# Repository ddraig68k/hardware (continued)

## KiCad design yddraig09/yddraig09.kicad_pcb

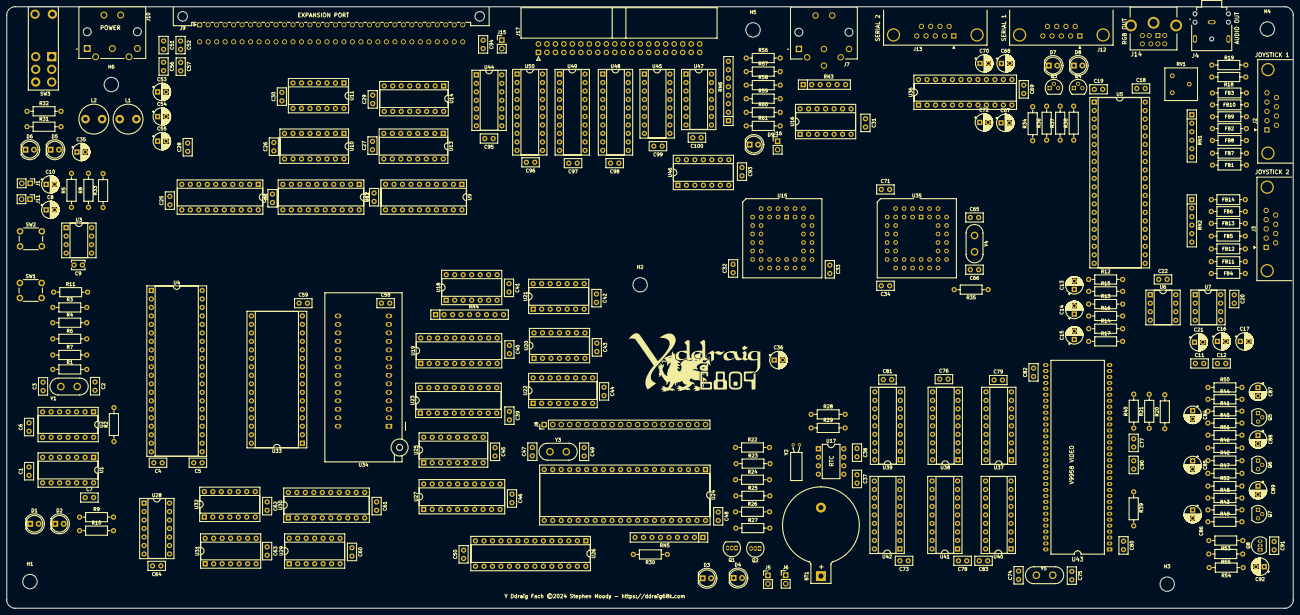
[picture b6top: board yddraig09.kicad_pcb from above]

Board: 4 copper layers, 385.0 x 180.0 mm, 283 parts (0 on the bottom side), 366 nets, no tracks yet.

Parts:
BT1: CR2032; BatteryHolder_Keystone_103_1x20mm
C1, C4, C5, C6, C18, C19, C20, C22, C23, C24, C25, C26, C27, C28, C29, C30, C31, C32, C33, C34, C37, C38, C39, C40, C41, C42, C43, C44, C45, C46, C48, C50, C51, C52, C56, C57, C58, C59, C60, C61, C62, C63, C64, C69, C71, C73, C76, C77, C78, C79, C80, C81, C82, C83, C90, C91, C93, C94, C95, C96, C97, C98, C99, C100: 100nF; C_Disc_D5.0mm_W2.5mm_P2.50mm
C2, C3, C47, C49, C65, C66, C74, C75: 22pF; C_Disc_D5.0mm_W2.5mm_P2.50mm
C7: 5pF; C_Disc_D5.0mm_W2.5mm_P2.50mm
C8, C10, C13, C14, C15, C16, C84, C85, C86: 10uF; CP_Radial_D5.0mm_P2.50mm
C9: 10nF; C_Disc_D3.8mm_W2.6mm_P2.50mm
C11, C12: 100nf; C_Disc_D5.0mm_W2.5mm_P2.50mm
C17: 1uF; CP_Radial_D5.0mm_P2.50mm
C21, C87, C88, C89, C92: 220uF; CP_Radial_D5.0mm_P2.50mm
C35, C36, C53, C54, C55: 47uF; CP_Radial_D5.0mm_P2.50mm
C67, C68, C70, C72: 0.1uF; CP_Radial_D5.0mm_P2.50mm
D1, D2, D3, D4, D5, D6, D7, D8: GREEN; LED_D5.0mm
D9: BLUE; LED_D5.0mm
FB1, FB2, FB3, FB4, FB5, FB6, FB7, FB8, FB9, FB10, FB11, FB12, FB13, FB14: 1mH; L_Axial_L6.6mm_D2.7mm_P10.16mm_Horizontal_Vishay_IM-2
H1, H2, H3, H4, H5, H6: MountingHole; MountingHole_4.3mm_M4
J1: ExtReset; PinHeader_1x02_P2.54mm_Vertical
J2: Joystick 2; DSUB-9_Male_Horizontal_P2.77x2.84mm_EdgePinOffset4.94mm_Hou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
J3: Joystick 1; DSUB-9_Male_Horizontal_P2.77x2.84mm_EdgePinOffset4.94mm_Hou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
J4: Audio Out; SWITCHCRAFT_35RAPC2BHN2
J5: ExtUSR1; PinHeader_1x02_P2.54mm_Vertical
J6: ExtUSR2; PinHeader_1x02_P2.54mm_Vertical
J7: IEC PORT; CUI_SDS-60J
J8: Keyboard; PinHeader_1x20_P2.54mm_Vertical
J9: Expansion; DIN41612_C_2x32_Male_Horizontal_THT
J10: 57PC5F; SWITCHCRAFT_57PC5F
J11: PwrLED; PinHeader_1x02_P2.54mm_Vertical
J12: Serial 1; DSUB-9_Male_Horizontal_P2.77x2.84mm_EdgePinOffset4.94mm_Hou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
J13: Serial 2; DSUB-9_Male_Horizontal_P2.77x2.84mm_EdgePinOffset4.94mm_Hou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
J14: RGB Video; MINI-DIN-8-TE_57492681
J15: IDE 5V; PinHeader_1x02_P2.54mm_Vertical
J16: IDE LED; PinHeader_1x02_P2.54mm_Vertical
J17: IDE_Interface; IDC-Header_2x20_P2.54mm_Horizontal
L1, L2: 22uH; L_Radial_D8.7mm_P5.00mm_Fastron_07HCP
Q1, Q2: BC549; TO-92_Inline
Q3, Q4, Q5, Q6, Q7: 2N4403; TO-92
Q8: 2N3904; TO-92_Inline
R1: 4M7; R_Axial_DIN0207_L6.3mm_D2.5mm_P10.16mm_Horizontal
R2: 2K2; R_Axial_DIN0207_L6.3mm_D2.5mm_P10.16mm_Horizontal
R3, R4, R6, R7: 4k7; R_Axial_DIN0207_L6.3mm_D2.5mm_P10.16mm_Horizontal
R5, R30, R35, R56, R57, R58, R59: 10K; R_Axial_DIN0207_L6.3mm_D2.5mm_P10.16mm_Horizontal
R8: 38K; R_Axial_DIN0207_L6.3mm_D2.5mm_P10.16mm_Horizontal
R9, R10, R12, R13, R14, R20, R21, R22, R25, R41, R42, R43, R53: 1K; R_Axial_DIN0207_L6.3mm_D2.5mm_P10.16mm_Horizontal
R11, R15, R16, R17, R28, R29, R39, R40: 4K7; R_Axial_DIN0207_L6.3mm_D2.5mm_P10.16mm_Horizontal
R18, R19, R50, R51, R52, R54: 100R; R_Axial_DIN0207_L6.3mm_D2.5mm_P10.16mm_Horizontal
R23, R24, R26, R27, R60, R61: 330R; R_Axial_DIN0207_L6.3mm_D2.5mm_P10.16mm_Horizontal
R31: 270R; R_Axial_DIN0207_L6.3mm_D2.5mm_P10.16mm_Horizontal
R32: 750R; R_Axial_DIN0207_L6.3mm_D2.5mm_P10.16mm_Horizontal
R33, R34, R36, R37, R38: 150R; R_Axial_DIN0207_L6.3mm_D2.5mm_P10.16mm_Horizontal
R44, R46, R48: 27K; R_Axial_DIN0207_L6.3mm_D2.5mm_P10.16mm_Horizontal
R45, R47, R49: 12K; R_Axial_DIN0207_L6.3mm_D2.5mm_P10.16mm_Horizontal
R55: 220R; R_Axial_DIN0207_L6.3mm_D2.5mm_P10.16mm_Horizontal
RN1, RN2: 4K7; R_Array_SIP6
RN3: 10K; R_Array_SIP6
RN4: 4K7; R_Array_SIP9
RN5: 10K; R_Array_SIP9
RN6: 22R; R_Array_SIP8
RV1: 10K; Potentiometer_Bourns_3386F_Vertical
SW1: NMI; SW_PUSH_6mm_H4.3mm
SW2: Reset; SW_PUSH_6mm_H4.3mm
SW3: PowerSwitch; M2022_Rocker_Switch
U1: 74LS73; DIP-14_W7.62mm_Socket
U2: 74HCT04; DIP-14_W7.62mm_Socket
U3: NE555P; DIP-8_W7.62mm_Socket
U4: MC68B09E; DIP-40_W15.24mm_Socket
U5: YM2203; DIP-40_W15.24mm_Socket
U6: YM3014B; DIP-8_W7.62mm_Socket
U7: NE5532; DIP-8_W7.62mm_Socket
U8, U9, U12, U50: 74LS245; DIP-20_W7.62mm_Socket
U10, U13, U25: 74LS138; DIP-16_W7.62mm_Socket
U11: 74LS21; DIP-14_W7.62mm_Socket
U14, U45: 74LS139; DIP-16_W7.62mm_Socket
U15: W65C22S; PLCC-44_THT-Socket
U16: 74LS06; DIP-14_W7.62mm_Socket
U17: DS1307+; DIP-8_W7.62mm
U18, U20, U28, U46: 74LS32; DIP-14_W7.62mm_Socket
U19, U48, U49: 74LS574; DIP-20_W7.62mm_Socket
U21: 74LS11; DIP-14_W7.62mm_Socket
U22: 74LS147; DIP-16_W7.62mm_Socket
U23: 74LS540; DIP-20_W7.62mm_Socket
U24: AT89C51-24PI; DIP-40_W15.24mm_Socket
U26: IDT7201; DIP-28_W7.62mm_Socket
U27: 74HCT541; DIP-20_W7.62mm_Socket
U29: 74LS27; DIP-14_W7.62mm_Socket
U30: 74HCT273; DIP-20_W7.62mm_Socket
U31, U32, U44: 74LS08; DIP-14_W7.62mm_Socket
U33: AS6C4008-55PCN; DIP-32_W15.24mm_Socket
U34: AT28C256B; DIP_Socket-28_W11.9_W12.7_W15.24_W17.78_W18.5_3M_228-1277-0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
U35: SC26C92C1A; PLCC-44_THT-Socket
U36: MAX208; DIP-24_W7.62mm_Socket
U37, U38, U39, U40, U41, U42: 41464; DIP-18_W7.62mm_Socket
U43: V9958; DIP-64-V9958
U47: 74LS74; DIP-14_W7.62mm_Socket
Y1: 8Mhz; Crystal_HC50_Vertical
Y2: Crystal; Crystal_C38-LF_D3.0mm_L8.0mm_Horizontal
Y3: 12Mhz; Crystal_HC50_Vertical
Y4: 3.6864Mhz; Crystal_HC50_Vertical
Y5: 21.443Mhz; Crystal_HC50_Vertical

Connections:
+5V: C1.1, C4.1, C5.1, C6.1, C18.1, C19.1, C20.1, C21.1, C22.1, C23.1, C24.1, C25.1, C26.1, C27.1, C28.1, C29.1, C30.1, C31.1, C32.1, C33.1, C34.1, C35.1, C36.1, C37.1, C38.1, C39.1, C40.1, C41.1, C42.1, C43.1, C44.1, C45.1, C46.1, C48.1, C50.1, C54.1, C55.1, C56.1, C57.1, C58.1, C59.1, C60.1, C61.1, C62.1, C63.1, C64.1, C69.1, C71.1, C72.2, C73.1, C76.1, C77.1, C78.1, C79.1, C80.1, C81.1, C83.1, C90.1, C91.1, C93.1, C94.1, C95.1, C96.1, C97.1, C98.1, C99.1, C100.1, D5.2 (A), D9.2 (A), FB2.1, FB5.1, J9.A1, J9.C1, J11.1, J14.5, J15.2, J16.2, L2.2, Q3.1 (E), Q4.1 (E), Q8.3 (C), R3.1, R4.1, R5.1, R6.1, R7.1, R8.1, R20.1, R21.1, R23.1, R24.1, R26.1, R27.1, R28.1, R29.1, R30.1, R35.1, R39.2, R40.2, R44.1, R46.1, R48.1, R50.1, R51.1, R52.1, R56.2, R58.2, R59.2, RN1.1 (common), RN2.1 (common), RN3.1 (common), RN4.1 (common), RN5.1 (common), U1.2 (~R), U1.4 (VCC), U1.6 (~R), U2.14 (VCC), U3.4 (R), U3.8 (VCC), U4.7 (VCC), U5.21 (VDD), U6.1 (VDD), U7.8 (V+), U8.20 (VCC), U9.20 (VCC), U10.6 (E3), U10.16 (VCC), U11.9, U11.10, U11.14 (VCC), U12.20 (VCC), U13.6 (E3), U13.16 (VCC), U14.16 (VCC), U15.21 (VDD), U15.26 (CS1), U16.14 (VCC), U17.8 (VCC), U18.14 (VCC), U19.20 (VCC), U20.14 (VCC), U21.14 (VCC), U22.5 (E8), U22.10 (E9), U22.16 (VCC), U23.6 (A4), U23.7 (A5), U23.8 (A6), U23.9 (A7), U23.20 (VCC), U24.40 (VCC), U25.6 (E3), U25.16 (VCC), U26.23 (FL), U26.28 (VCC), U27.20 (VCC), U28.14 (VCC), U29.14 (VCC), U30.20 (VCC), U31.14 (VCC), U32.14 (VCC), U33.32 (VCC), U34.28 (VCC), U35.44 (VCC), U36.9 (VCC), U37.9 (VCC), U38.9 (VCC), U39.9 (VCC), U40.9 (VCC), U41.9 (VCC), U42.9 (VCC), U43.21 (VDD/DAC), U43.58 (VDD), U44.14 (VCC), U45.16 (VCC), U46.14 (VCC), U47.14 (VCC), U48.20 (VCC), U49.20 (VCC), U50.20 (VCC)
+12V: C51.1, C52.1, C53.1, D6.2 (A), J9.A2, J9.C2, L1.2
/6809 CPU/CLK_8MHZ: C7.1, R2.1, U1.1 (C), U1.5 (C)
/6809 CPU/CLOCK_E: J9.C8, U1.10 (K), U1.12 (Q), U4.34 (E), U5.38 (CLK-M), U14.3 (A1), U15.27 (PHI2), U47.3 (C), U47.11 (C)
/6809 CPU/CLOCK_Q: J9.C7, U1.9 (Q), U1.14 (J), U4.35 (Q)
/6809 CPU/CPU_A0: U4.8 (A0), U9.18 (B0), U33.12 (A0), U34.10 (A0)
/6809 CPU/CPU_A1: U4.9 (A1), U9.17 (B1), U33.11 (A1), U34.9 (A1)
/6809 CPU/CPU_A2: U4.10 (A2), U9.16 (B2), U33.10 (A2), U34.8 (A2)
/6809 CPU/CPU_A3: U4.11 (A3), U9.15 (B3), U33.9 (A3), U34.7 (A3)
/6809 CPU/CPU_A4: U4.12 (A4), U9.14 (B4), U33.8 (A4), U34.6 (A4)
/6809 CPU/CPU_A5: U4.13 (A5), U9.13 (B5), U13.1 (A0), U33.7 (A5), U34.5 (A5)
/6809 CPU/CPU_A6: U4.14 (A6), U9.12 (B6), U13.2 (A1), U33.6 (A6), U34.4 (A6)
/6809 CPU/CPU_A7: U4.15 (A7), U9.11 (B7), U13.3 (A2), U33.5 (A7), U34.3 (A7)
/6809 CPU/CPU_A8: U4.16 (A8), U12.18 (B0), U33.27 (A8), U34.25 (A8)
/6809 CPU/CPU_A9: U4.17 (A9), U12.17 (B1), U33.26 (A9), U34.24 (A9)
/6809 CPU/CPU_A10: U4.18 (A10), U12.16 (B2), U33.23 (A10), U34.21 (A10)
/6809 CPU/CPU_A11: U4.19 (A11), U12.15 (B3), U33.25 (A11), U34.23 (A11)
/6809 CPU/CPU_A12: U4.20 (A12), U12.14 (B4), U33.4 (A12), U34.2 (A12)
/6809 CPU/CPU_A13: U4.21 (A13), U10.1 (A0), U12.13 (B5), U33.28 (A13), U34.26 (A13)
/6809 CPU/CPU_A14: U4.22 (A14), U10.2 (A1), U12.12 (B6)
/6809 CPU/CPU_A15: U4.23 (A15), U10.3 (A2), U12.11 (B7)
/6809 CPU/RD~WR: U4.32 (R/~W), U8.1 (A->B), U14.2 (A0)
/6809 CPU/RESET: J9.C6, U2.13, U3.3 (Q), U24.9 (RESET), U35.38 (RESET)
/6809 CPU/~FIRQ: J9.C4, R4.2, U4.4 (~FIRQ)
/6809 CPU/~HALT: J9.A4, R3.2, U4.40 (~HALT)
/6809 CPU/~IRQ: R6.2, U4.3 (~IRQ), U21.12
/6809 CPU/~NMI: J9.C3, R7.2, SW1.2 (B), U4.2 (~NMI)
/6809 CPU/~RESET: J9.C5, J17.1 (~RESET), U2.12, U4.37 (~RESET), U5.24 (~RESET), U15.37 (~RESET), U16.9, U30.1 (~Mr), U43.9 (~RESET)
/Audio/A0: J9.C30, RN6.1 (R1.1), U5.37 (A0), U9.2 (A0), U15.42 (RS0), U25.1 (A0), U35.2 (A0), U43.29 (MODE0)
/Audio/A1: J9.C29, RN6.3 (R2.1), U9.3 (A1), U15.41 (RS1), U35.4 (A1), U43.28 (MODE1)
/Audio/A2: J9.C28, RN6.5 (R3.1), U9.4 (A2), U15.40 (RS2), U35.6 (A2)
/Audio/A3: J9.C27, RN6.7 (R4.1), U9.5 (A3), U15.39 (RS3), U35.7 (A3)
/Audio/A4: J9.C26, U9.6 (A4)
/Audio/A5: J9.C25, U9.7 (A5)
/Audio/A6: J9.C24, U9.8 (A6)
/Audio/A7: J9.C23, U9.9 (A7)
/Audio/A8: J9.C22, U12.2 (A0)
/Audio/A9: J9.C21, U12.3 (A1)
/Audio/A10: J9.C20, U12.4 (A2)
/Audio/A11: J9.C19, U12.5 (A3)
/Audio/A12: J9.C18, U12.6 (A4)
/Audio/A13: J9.C17, U12.7 (A5)
/Audio/A14: J9.C16, U12.8 (A6)
/Audio/A15: J9.C15, U12.9 (A7)
/Audio/AUDIO_L: J4.1, J14.1, R18.2
/Audio/AUDIO_OUT: C17.2, R15.1, R16.1, R17.1, RV1.1
/Audio/AUDIO_R: J4.3, J14.2, R19.2
/Audio/D0: J9.A12, U5.40 (D0), U8.2 (A0), U15.36 (D0), U19.2 (D0), U23.18 (Y0), U26.9 (Q0), U27.18 (Y0), U35.28 (D0), U43.40 (D0), U50.2 (A0)
/Audio/D1: J9.A11, U5.2 (D1), U8.3 (A1), U15.35 (D1), U19.3 (D1), U23.17 (Y1), U26.10 (Q1), U27.17 (Y1), U35.18 (D1), U43.39 (D1), U50.3 (A1)
/Audio/D2: J9.A10, U5.3 (D2), U8.4 (A2), U15.34 (D2), U19.4 (D2), U23.16 (Y2), U26.11 (Q2), U27.16 (Y2), U35.27 (D2), U43.38 (D2), U50.4 (A2)
/Audio/D3: J9.A9, U5.4 (D3), U8.5 (A3), U15.32 (D3), U19.5 (D3), U23.15 (Y3), U26.12 (Q3), U27.15 (Y3), U35.19 (D3), U43.37 (D3), U50.5 (A3)
/Audio/D4: J9.A8, U5.5 (D4), U8.6 (A4), U15.31 (D4), U19.6 (D4), U23.14 (Y4), U26.16 (Q4), U27.14 (Y4), U35.26 (D4), U43.36 (D4), U50.6 (A4)
/Audio/D5: J9.A7, U5.6 (D5), U8.7 (A5), U15.30 (D5), U19.7 (D5), U23.13 (Y5), U26.17 (Q5), U27.13 (Y5), U35.20 (D5), U43.35 (D5), U50.7 (A5)
/Audio/D6: J9.A6, U5.7 (D6), U8.8 (A6), U15.29 (D6), U19.8 (D6), U23.12 (Y6), U26.18 (Q6), U27.12 (Y6), U35.25 (D6), U43.34 (D6), U50.8 (A6)
/Audio/D7: J9.A5, U5.8 (D7), U8.9 (A7), U15.28 (D7), U19.9 (D7), U23.11 (Y7), U26.19 (Q7), U27.11 (Y7), U35.21 (D7), U43.32 (D7), U50.9 (A7)
/Audio/~CS_SND: U5.34 (~CS), U13.10 (O5)
/Audio/~IRQ_SND: RN4.6 (R5), U5.25 (~IRQ), U20.1
/Decode Logic/~BANKSEL: U13.15 (O0), U30.11 (Cp)
/Decode Logic/~CS_EXP: J9.A15, U10.11 (O4)
/Decode Logic/~CS_IDE: U13.14 (O1), U44.5, U46.2, U46.5
/Decode Logic/~CS_IRQEN: U13.7 (O7), U18.12, U23.19 (G2)
/Decode Logic/~CS_KBD: U13.12 (O3), U25.4 (E1)
/Decode Logic/~CS_RAM: U11.6, U33.22 (CE#)
/Decode Logic/~CS_ROM: U11.8, U34.20 (~CE)
/Decode Logic/~CS_UART: U13.13 (O2), U35.39 (~CE)
/Decode Logic/~CS_VDP: U13.11 (O4), U14.15 (E)
/Decode Logic/~CS_VIA: U13.9 (O6), U15.25 (~CS2)
/Decode Logic/~IOSEL: U10.10 (O5), U13.5 (E2)
/Decode Logic/~MEM0: U10.15 (O0), U11.1
/Decode Logic/~MEM2: U10.14 (O1), U11.2
/Decode Logic/~MEM4: U10.13 (O2), U11.4
/Decode Logic/~MEM6: U10.12 (O3), U11.5
/Decode Logic/~MEMC: U10.9 (O6), U11.12
/Decode Logic/~MEME: U10.7 (O7), U11.13
/Decode Logic/~VDP_RD: R20.2, U14.11 (O1), U43.31 (~CSR)
/Decode Logic/~VDP_WR: R21.2, U14.10 (O2), U43.30 (~CSW)
/IDE Interface/IDE_A0: J17.35 (A0), RN6.2 (R1.2)
/IDE Interface/IDE_A1: J17.33 (A1), RN6.4 (R2.2)
/IDE Interface/IDE_A2: J17.36 (A2), RN6.6 (R3.2)
/IDE Interface/IDE_A3: RN6.8 (R4.2), U45.2 (A0), U45.14 (A0), U46.9
/IDE Interface/IDE_ACTIVE: J17.39 (~ACTIVE), R60.2, R61.2
/IDE Interface/IDE_D0: J17.17 (D0), U48.19 (Q0), U49.2 (D0), U50.18 (B0)
/IDE Interface/IDE_D1: J17.15 (D1), U48.18 (Q1), U49.3 (D1), U50.17 (B1)
/IDE Interface/IDE_D2: J17.13 (D2), U48.17 (Q2), U49.4 (D2), U50.16 (B2)
/IDE Interface/IDE_D3: J17.11 (D3), U48.16 (Q3), U49.5 (D3), U50.15 (B3)
/IDE Interface/IDE_D4: J17.9 (D4), U48.15 (Q4), U49.6 (D4), U50.14 (B4)
/IDE Interface/IDE_D5: J17.7 (D5), U48.14 (Q5), U49.7 (D5), U50.13 (B5)
/IDE Interface/IDE_D6: J17.5 (D6), U48.13 (Q6), U49.8 (D6), U50.12 (B6)
/IDE Interface/IDE_D7: J17.3 (D7), U48.12 (Q7), U49.9 (D7), U50.11 (B7)
/IDE Interface/IDE_D8: J17.4 (D8), U48.2 (D0), U49.19 (Q0)
/IDE Interface/IDE_D9: J17.6 (D9), U48.3 (D1), U49.18 (Q1)
/IDE Interface/IDE_D10: J17.8 (D10), U48.4 (D2), U49.17 (Q2)
/IDE Interface/IDE_D11: J17.10 (D11), U48.5 (D3), U49.16 (Q3)
/IDE Interface/IDE_D12: J17.12 (D12), U48.6 (D4), U49.15 (Q4)
/IDE Interface/IDE_D13: J17.14 (D13), U48.7 (D5), U49.14 (Q5)
/IDE Interface/IDE_D14: J17.16 (D14), U48.8 (D6), U49.13 (Q6)
/IDE Interface/IDE_D15: J17.18 (D15), U48.9 (D7), U49.12 (Q7)
/IO/ATN_OUT: U15.4 (PA2), U16.1
/IO/CLK_IN: J7.4, RN3.4 (R3), U15.6 (PA4), U16.6
/IO/CLK_OUT: U15.3 (PA1), U16.5
/IO/DATA_IN: J7.5, RN3.6 (R5), U15.5 (PA3), U16.4
/IO/DATA_OUT: U15.2 (PA0), U16.3
/IO/EXPIO_C1: J9.A19, U15.19 (CB1)
/IO/EXPIO_C2: J9.A20, U15.20 (CB2)
/IO/EXPIO_P0: J9.A23, U15.10 (PB0)
/IO/EXPIO_P1: J9.A24, U15.12 (PB1)
/IO/EXPIO_P2: J9.A25, U15.13 (PB2)
/IO/EXPIO_P3: J9.A26, U15.14 (PB3)
/IO/EXPIO_P4: J9.A27, U15.15 (PB4)
/IO/EXPIO_P5: J9.A28, U15.16 (PB5)
/IO/IEC_ATTN: J7.3, RN3.2 (R1), U16.2
/IO/SCL: J9.C10, R28.2, U15.17 (PB6), U17.6 (SCL)
/IO/SDA: J9.C11, R29.2, U15.18 (PB7), U17.5 (SDA)
/IO/USER1: R22.2, U15.8 (PA6)
/IO/USER2: R25.2, U15.9 (PA7)
/IO/~IEC_RESET: J7.6, RN3.5 (R4), U16.8
/IO/~IEC_SRQIN: J7.1, RN3.3 (R2), U15.7 (PA5)
/IO/~IRQ_VIA: RN4.4 (R3), U15.23 (~IRQ), U18.9
/IO/~KBD_INT: RN4.3 (R2), U16.12, U18.4
/Interrupts/~IRQ0: R35.2, RN4.2 (R1), U18.1, U35.24 (~INTR)
/Interrupts/~IRQ3: RN4.5 (R4), U20.12, U43.25 (~INT)
/Interrupts/~IRQ5: J9.C13, RN4.7 (R6), U20.4
/Interrupts/~IRQ6: J9.A13, RN4.8 (R7), U20.9
/Keyboard/SCDAT0: U24.21 (P2.0(A8)), U26.6 (D0)
/Keyboard/SCDAT1: U24.22 (P2.1(A9)), U26.5 (D1)
/Keyboard/SCDAT2: U24.23 (P2.2(A10)), U26.4 (D2)
/Keyboard/SCDAT3: U24.24 (P2.3(A11)), U26.3 (D3)
/Keyboard/SCDAT4: U24.25 (P2.4(A12)), U26.27 (D4)
/Keyboard/SCDAT5: U24.26 (P2.5(A13)), U26.26 (D5)
/Keyboard/SCDAT6: U24.27 (P2.6(A14)), U26.25 (D6)
/Keyboard/SCDAT7: U24.28 (P2.7(A15)), U26.24 (D7)
/Keyboard/~COL0: J8.20, U24.1 (P1.0)
/Keyboard/~COL1: J8.19, U24.2 (P1.1)
/Keyboard/~COL2: J8.18, U24.3 (P1.2)
/Keyboard/~COL3: J8.17, U24.4 (P1.3)
/Keyboard/~COL4: J8.16, U24.5 (P1.4)
/Keyboard/~COL5: J8.15, U24.6 (P1.5)
/Keyboard/~COL6: J8.14, U24.7 (P1.6)
/Keyboard/~COL7: J8.13, U24.8 (P1.7)
/Keyboard/~COL8: J8.1, U24.14 (P3.4(T0))
/Keyboard/~FIFO_CLR: U24.17 (P3.7(~RD)), U26.22 (CLR)
/Keyboard/~FIFO_EMPTY: U16.13, U26.21 (EF), U27.2 (A0)
/Keyboard/~FIFO_FULL: U26.8 (FF), U27.3 (A1)
/Keyboard/~FIFO_RD: U25.15 (O0), U26.15 (RD)
/Keyboard/~FIFO_WR: U24.16 (P3.6(~WR)), U26.1 (WR)
/Keyboard/~KBD_STATUS: U25.14 (O1), U27.1 (G1)
/Keyboard/~ROW0: J8.12, RN5.2 (R1), U24.39 (P0.0(AD0))
/Keyboard/~ROW1: J8.11, RN5.3 (R2), U24.38 (P0.1(AD1))
/Keyboard/~ROW2: J8.10, RN5.4 (R3), U24.37 (P0.2(AD2))
/Keyboard/~ROW3: J8.9, RN5.5 (R4), U24.36 (P0.3(AD3))
/Keyboard/~ROW4: J8.8, RN5.6 (R5), U24.35 (P0.4(AD4))
/Keyboard/~ROW5: J8.7, RN5.7 (R6), U24.34 (P0.5(AD5))
/Keyboard/~ROW6: J8.6, RN5.8 (R7), U24.33 (P0.6(AD6))
/Keyboard/~ROW7: J8.5, RN5.9 (R8), U24.32 (P0.7(AD7))
/Keyboard/~ROW8: J8.3, R30.2, U24.15 (P3.5(T1))
/RAM and ROM/A14: U31.1, U31.4, U32.1, U32.4, U32.9, U32.12
/RAM and ROM/BSEL0: U28.1, U29.1, U30.2 (Q0)
/RAM and ROM/BSEL1: U29.2, U30.5 (Q1), U32.10
/RAM and ROM/BSEL2: U29.13, U30.6 (Q2), U32.13
/RAM and ROM/BSEL3: U29.3, U30.9 (Q3), U32.2
/RAM and ROM/BSEL4: U29.4, U30.12 (Q4), U32.5
/RAM and ROM/BSEL5: U30.15 (Q5), U31.2
/RAM and ROM/CPU_D0: U4.31 (D0), U8.18 (B0), U30.3 (D0), U33.13 (DQ0), U34.11 (I/O0)
/RAM and ROM/CPU_D1: U4.30 (D1), U8.17 (B1), U30.4 (D1), U33.14 (DQ1), U34.12 (I/O1)
/RAM and ROM/CPU_D2: U4.29 (D2), U8.16 (B2), U30.7 (D2), U33.15 (DQ2), U34.13 (I/O2)
/RAM and ROM/CPU_D3: U4.28 (D3), U8.15 (B3), U30.8 (D3), U33.17 (DQ3), U34.15 (I/O3)
/RAM and ROM/CPU_D4: U4.27 (D4), U8.14 (B4), U30.13 (D4), U33.18 (DQ4), U34.16 (I/O4)
/RAM and ROM/CPU_D5: U4.26 (D5), U8.13 (B5), U30.14 (D5), U33.19 (DQ5), U34.17 (I/O5)
/RAM and ROM/CPU_D6: U4.25 (D6), U8.12 (B6), U30.17 (D6), U33.20 (DQ6), U34.18 (I/O6)
/RAM and ROM/CPU_D7: U4.24 (D7), U8.11 (B7), U30.18 (D7), U33.21 (DQ7), U34.19 (I/O7)
/RAM and ROM/RAMB0: U31.6, U33.3 (A14)
/RAM and ROM/RAMB1: U32.8, U33.31 (A15)
/RAM and ROM/RAMB2: U32.11, U33.2 (A16)
/RAM and ROM/RAMB3: U32.3, U33.30 (A17)
/RAM and ROM/RAMB4: U32.6, U33.1 (A18)
/RAM and ROM/ROMBANK: U31.3, U34.1 (A14)
/Serial Ports/CTSA: U35.8 (IP0), U36.4 (ROUT2)
/Serial Ports/CTSB: U35.5 (IP1), U36.17 (ROUT4)
/Serial Ports/RTSA: U35.32 (OP0), U36.18 (DIN2)
/Serial Ports/RTSB: U35.14 (OP1), U36.21 (DIN4)
/Serial Ports/RXDA: R37.2, U35.33 (TxDA), U36.5 (DIN1)
/Serial Ports/RXDB: U35.13 (TxDB), U36.19 (DIN3)
/Serial Ports/TXDA: R34.2, U35.35 (RxDA), U36.6 (ROUT1)
/Serial Ports/TXDB: U35.11 (RxDB), U36.22 (ROUT3)
/Video/BLUE: C86.1, R43.1, U43.24 (BLUE)
/Video/GREEN: C85.1, R42.1, U43.22 (GREEN)
/Video/RED: C84.1, R41.1, U43.23 (RED)
/Video/VA0: U37.14 (A0), U38.14 (A0), U39.14 (A0), U40.14 (A0), U41.14 (A0), U42.14 (A0), U43.49 (VA0)
/Video/VA1: U37.13 (A1), U38.13 (A1), U39.13 (A1), U40.13 (A1), U41.13 (A1), U42.13 (A1), U43.50 (VA1)
/Video/VA2: U37.12 (A2), U38.12 (A2), U39.12 (A2), U40.12 (A2), U41.12 (A2), U42.12 (A2), U43.51 (VA2)
/Video/VA3: U37.11 (A3), U38.11 (A3), U39.11 (A3), U40.11 (A3), U41.11 (A3), U42.11 (A3), U43.52 (VA3)
/Video/VA4: U37.8 (A4), U38.8 (A4), U39.8 (A4), U40.8 (A4), U41.8 (A4), U42.8 (A4), U43.53 (VA4)
/Video/VA5: U37.7 (A5), U38.7 (A5), U39.7 (A5), U40.7 (A5), U41.7 (A5), U42.7 (A5), U43.54 (VA5)
/Video/VA6: U37.6 (A6), U38.6 (A6), U39.6 (A6), U40.6 (A6), U41.6 (A6), U42.6 (A6), U43.55 (VA6)
/Video/VA7: U37.10 (A7), U38.10 (A7), U39.10 (A7), U40.10 (A7), U41.10 (A7), U42.10 (A7), U43.56 (VA7)
/Video/VD0: U37.2 (D0), U38.2 (D0), U39.2 (D0), U43.41 (VD0)
/Video/VD1: U37.3 (D1), U38.3 (D1), U39.3 (D1), U43.42 (VD1)
/Video/VD2: U37.15 (D2), U38.15 (D2), U39.15 (D2), U43.43 (VD2)
/Video/VD3: U37.17 (D3), U38.17 (D3), U39.17 (D3), U43.44 (VD3)
/Video/VD4: U40.2 (D0), U41.2 (D0), U42.2 (D0), U43.45 (VD4)
/Video/VD5: U40.3 (D1), U41.3 (D1), U42.3 (D1), U43.46 (VD5)
/Video/VD6: U40.15 (D2), U41.15 (D2), U42.15 (D2), U43.47 (VD6)
/Video/VD7: U40.17 (D3), U41.17 (D3), U42.17 (D3), U43.48 (VD7)
/Video/VR~W: U37.4 (~WE), U38.4 (~WE), U39.4 (~WE), U40.4 (~WE), U41.4 (~WE), U42.4 (~WE), U43.57 (R/~W)
/Video/~CAS0: U39.16 (~CAS), U42.16 (~CAS), U43.61 (~CAS0)
/Video/~CAS1: U37.16 (~CAS), U40.16 (~CAS), U43.60 (~CAS1)
/Video/~CASX: U38.16 (~CAS), U41.16 (~CAS), U43.59 (~CASX)
/Video/~CSYNC: R53.2, U43.6 (~CSYNC)
/Video/~RAS: U37.5 (~RAS), U38.5 (~RAS), U39.5 (~RAS), U40.5 (~RAS), U41.5 (~RAS), U42.5 (~RAS), U43.62 (~RAS)
/VideoOut/BOUT: C89.2, J14.6
/VideoOut/GOUT: C88.2, J14.7
/VideoOut/ROUT: C87.2, J14.8
/VideoOut/SYNCOUT: J14.3, R55.1
/~RD: J9.A22, U5.36 (~RD), U14.7 (O3), U14.13 (A1), U23.1 (G1), U25.5 (E2), U33.24 (OE#), U34.22 (~OE), U35.10 (~RD), U46.1
/~WR: J9.A21, U5.35 (~WR), U14.6 (O2), U14.14 (A0), U15.24 (R/~W), U18.13, U33.29 (WE#), U34.27 (~WE), U35.9 (~WR), U46.4
GND: BT1.2 (-), C1.2, C2.2, C3.2, C4.2, C5.2, C6.2, C7.2, C8.2, C9.2, C10.2, C11.2, C12.2, C16.2, C18.2, C19.2, C20.2, C21.2, C22.2, C23.2, C24.2, C25.2, C26.2, C27.2, C28.2, C29.2, C30.2, C31.2, C32.2, C33.2, C34.2, C35.2, C36.2, C37.2, C38.2, C39.2, C40.2, C41.2, C42.2, C43.2, C44.2, C45.2, C46.2, C47.2, C48.2, C49.2, C50.2, C51.2, C52.2, C53.2, C54.2, C55.2, C56.2, C57.2, C58.2, C59.2, C60.2, C61.2, C62.2, C63.2, C64.2, C65.2, C66.2, C69.2, C70.1, C71.2, C73.2, C74.2, C75.2, C76.2, C77.2, C78.2, C79.2, C80.2, C81.2, C82.1, C83.2, C90.2, C91.2, C93.2, C94.2, C95.2, C96.2, C97.2, C98.2, C99.2, C100.2, D1.1 (K), D2.1 (K), FB3.1, FB6.1, J1.2, J2.0 (PAD), J3.0 (PAD), J4.2, J7.2, J9.A31, J9.A32, J9.C31, J9.C32, J10.1, J10.2, J12.0 (PAD), J12.5, J13.0 (PAD), J13.5, J14.4, J17.2 (GND), J17.19 (GND), J17.22 (GND), J17.24 (GND), J17.26 (GND), J17.28 (CABLE_SEL), J17.30 (GND), J17.40 (GND), Q1.3 (E), Q2.3 (E), Q5.3 (C), Q6.3 (C), Q7.3 (C), R11.2, R12.2, R13.2, R14.2, R31.2, R32.2, R33.2, R36.2, R38.2, R41.2, R42.2, R43.2, R45.2, R47.2, R49.2, R54.2, R57.2, RV1.3, SW1.1 (A), SW2.1 (A), U1.11 (GND), U2.5, U2.7 (GND), U2.9, U2.11, U3.1 (GND), U4.1 (VSS), U5.1 (GND), U5.17 (AGND), U6.6 (GND), U7.4 (V-), U8.10 (GND), U8.19 (CE), U9.1 (A->B), U9.10 (GND), U9.19 (CE), U10.4 (E1), U10.5 (E2), U10.8 (GND), U11.7 (GND), U12.1 (A->B), U12.10 (GND), U12.19 (CE), U13.4 (E1), U13.8 (GND), U14.1 (E), U14.8 (GND), U15.1 (VSS), U16.7 (GND), U16.11, U17.4 (GND), U18.7 (GND), U19.1 (OE), U19.10 (GND), U20.7 (GND), U21.7 (GND), U22.8 (GND), U23.10 (GND), U24.20 (GND), U24.31 (~EA/VPP), U25.2 (A1), U25.3 (A2), U25.8 (GND), U26.2 (D8), U26.7 (XI), U26.14 (VSS), U27.4 (A2), U27.5 (A3), U27.6 (A4), U27.7 (A5), U27.8 (A6), U27.9 (A7), U27.10 (GND), U27.19 (G2), U28.4, U28.5, U28.7 (GND), U28.9, U28.10, U28.12, U28.13, U29.5, U29.7 (GND), U29.9, U29.10, U29.11, U30.10 (GND), U31.7 (GND), U31.12, U31.13, U32.7 (GND), U33.16 (VSS), U34.14 (GND), U35.22 (GND), U36.8 (GND), U37.1 (~OE), U37.18 (VSS), U38.1 (~OE), U38.18 (VSS), U39.1 (~OE), U39.18 (VSS), U40.1 (~OE), U40.18 (VSS), U41.1 (~OE), U41.18 (VSS), U42.1 (~OE), U42.18 (VSS), U43.1 (GND), U43.20 (GND/DAC), U44.7 (GND), U44.9, U44.10, U44.12, U44.13, U45.3 (A1), U45.8 (GND), U45.13 (A1), U46.7 (GND), U47.7 (GND), U48.10 (GND), U49.10 (GND), U50.10 (GND)
unnamed: BT1.1 (+), U17.3 (VBAT)
unnamed: C2.1, R1.1, U2.1, Y1.2
unnamed: C3.1, R1.2, U2.2, U2.3, Y1.1
unnamed: C13.1, R15.2
unnamed: C14.1, R16.2
unnamed: C15.1, R17.2
unnamed: C92.2, R55.2
unnamed: D1.2 (A), R9.2
unnamed: D2.2 (A), R10.2
unnamed: D3.2 (A), R24.2
unnamed: D3.1 (K), J5.2, Q1.1 (C)
unnamed: D4.2 (A), R27.2
unnamed: D4.1 (K), J6.2, Q2.1 (C)
unnamed: D5.1 (K), R31.1
unnamed: D6.1 (K), R32.1
unnamed: D7.2 (A), Q3.3 (C)
unnamed: D7.1 (K), R36.1
unnamed: D8.2 (A), Q4.3 (C)
unnamed: D8.1 (K), R38.1
unnamed: D9.1 (K), R61.1
unnamed: FB1.2, J2.6
unnamed: FB2.2, J2.7
unnamed: FB3.2, J2.8
unnamed: FB4.2, J3.6
unnamed: FB5.2, J3.7
unnamed: FB6.2, J3.8
unnamed: FB7.2, J2.1
unnamed: FB8.2, J2.2
unnamed: FB9.2, J2.3
unnamed: FB10.2, J2.4
unnamed: FB11.2, J3.1
unnamed: FB12.2, J3.2
unnamed: FB13.2, J3.3
unnamed: FB14.2, J3.4
unnamed: C8.1, J1.1, R5.2, SW2.2 (B), U3.2 (TR)
unnamed: J5.1, R23.2
unnamed: J6.1, R26.2
unnamed: J10.3, SW3.5 (B)
unnamed: J10.5, SW3.2 (B)
unnamed: J11.2, R33.1
unnamed: J15.1, J17.20 (KEY)
unnamed: J16.1, R60.1
unnamed: J17.21 (DMARQ), R57.1
unnamed: J17.25 (~DIOR), U44.1, U47.5 (Q), U50.1 (A->B)
unnamed: J17.23 (~DIOW), U46.11
unnamed: J17.29 (~DMACK), R59.1
unnamed: J17.37 (~IDE_CS0), U46.8
unnamed: J17.38 (~IDE_CS1), R58.1
unnamed: L1.1, SW3.3 (C)
unnamed: L2.1, SW3.6 (C)
unnamed: Q1.2 (B), R22.1
unnamed: Q2.2 (B), R25.1
unnamed: Q3.2 (B), R34.1
unnamed: Q4.2 (B), R37.1
unnamed: C84.2, Q5.2 (B), R44.2, R45.1
unnamed: C87.1, Q5.1 (E), R50.2
unnamed: C85.2, Q6.2 (B), R46.2, R47.1
unnamed: C88.1, Q6.1 (E), R51.2
unnamed: C86.2, Q7.2 (B), R48.2, R49.1
unnamed: C89.1, Q7.1 (E), R52.2
unnamed: Q8.2 (B), R53.1
unnamed: C92.1, Q8.1 (E), R54.1
unnamed: R2.2, U2.4
unnamed: R18.1, R19.1, RV1.2
unnamed: FB1.1, RN1.2 (R1), U5.30 (IOB4)
unnamed: FB10.1, RN1.3 (R2), U5.29 (IOB3)
unnamed: FB9.1, RN1.4 (R3), U5.28 (IOB2)
unnamed: FB8.1, RN1.5 (R4), U5.27 (IOB1)
unnamed: FB7.1, RN1.6 (R5), U5.26 (IOB0)
unnamed: FB4.1, RN2.2 (R1), U5.12 (IOA4)
unnamed: FB14.1, RN2.3 (R2), U5.13 (IOA3)
unnamed: FB13.1, RN2.4 (R3), U5.14 (IOA2)
unnamed: FB12.1, RN2.5 (R4), U5.15 (IOA1)
unnamed: FB11.1, RN2.6 (R5), U5.16 (IOA0)
unnamed: U1.7 (J), U1.13 (~Q)
unnamed: U1.3 (K), U1.8 (~Q)
unnamed: C9.1, U3.5 (CV)
unnamed: C10.1, R8.2, U3.6 (THR), U3.7 (DIS)
unnamed: R10.1, U4.6 (BA)
unnamed: R9.1, U4.5 (BS)
unnamed: R11.1, U4.39 (TSC)
unnamed: C15.2, R14.1, U5.20 (ANALOGA)
unnamed: C14.2, R13.1, U5.19 (ANALOGB)
unnamed: C13.2, R12.1, U5.18 (ANALOGC)
unnamed: U5.39 (CLK-S), U6.5 (CLOCK)
unnamed: U5.23 (OP-O), U6.4 (SD)
unnamed: U5.22 (SH), U6.3 (LOAD)
unnamed: C12.1, U6.8 (MP), U7.1, U7.2 (-)
unnamed: C16.1, U6.7 (RB), U7.3 (+)
unnamed: C11.1, U6.2 (ToBUFF), U7.5 (+)
unnamed: C17.1, U7.6 (-), U7.7
unnamed: U17.1 (X1), Y2.1
unnamed: U17.2 (X2), Y2.2
unnamed: U18.11, U19.11 (Cp)
unnamed: U18.2, U19.19 (Q0)
unnamed: U18.5, U19.18 (Q1)
unnamed: U18.10, U19.17 (Q2)
unnamed: U19.16 (Q3), U20.13
unnamed: U19.15 (Q4), U20.2
unnamed: U19.14 (Q5), U20.5
unnamed: U19.13 (Q6), U20.10
unnamed: U21.2, U21.6
unnamed: U21.8, U21.13
unnamed: U18.3, U21.1, U22.11 (E1)
unnamed: U18.6, U21.3, U22.12 (E2)
unnamed: U18.8, U21.4, U22.13 (E3)
unnamed: U20.11, U21.5, U22.1 (E4)
unnamed: U20.3, U21.9, U22.2 (E5)
unnamed: U20.6, U21.10, U22.3 (E6)
unnamed: U20.8, U21.11, U22.4 (E7)
unnamed: U22.9 (S0), U23.2 (A0)
unnamed: U22.7 (S1), U23.3 (A1)
unnamed: U22.6 (S2), U23.4 (A2)
unnamed: U22.14 (S3), U23.5 (A3)
unnamed: C47.1, U24.19 (XTAL1), Y3.1
unnamed: C49.1, U24.18 (XTAL2), Y3.2
unnamed: U28.2, U31.8
unnamed: U28.3, U31.5
unnamed: U29.6, U31.10
unnamed: U29.12, U31.9
unnamed: C66.1, U35.36 (X1/CLK), Y4.2
unnamed: C65.1, U35.37 (X2), Y4.1
unnamed: C67.1, U36.10 (C1+)
unnamed: C67.2, U36.12 (C1-)
unnamed: C68.1, U36.13 (C2+)
unnamed: C68.2, U36.14 (C2-)
unnamed: J12.3, U36.2 (DOUT1)
unnamed: J12.7, U36.1 (DOUT2)
unnamed: J13.3, U36.24 (DOUT3)
unnamed: J13.7, U36.20 (DOUT4)
unnamed: J12.2, U36.7 (RIN1)
unnamed: J12.8, U36.3 (RIN2)
unnamed: J13.2, U36.23 (RIN3)
unnamed: J13.8, U36.16 (RIN4)
unnamed: C72.1, U36.11 (V+)
unnamed: C70.2, U36.15 (V-)
unnamed: C82.2, U43.33 (VBB)
unnamed: C74.1, U43.63 (XTAL1), Y5.1
unnamed: C75.1, U43.64 (XTAL2), Y5.2
unnamed: R40.1, U43.27 (~HRESET)
unnamed: R39.1, U43.4 (~VRESET)
unnamed: U44.6, U46.10
unnamed: U45.1 (E), U46.3, U47.2 (D)
unnamed: U45.4 (O0), U48.11 (Cp)
unnamed: U45.5 (O1), U48.1 (OE)
unnamed: U45.15 (E), U46.6, U46.13, U47.12 (D)
unnamed: U45.11 (O1), U49.11 (Cp)
unnamed: R56.1, U47.1 (~R), U47.4 (~S), U47.10 (~S), U47.13 (~R)
unnamed: U44.2, U46.12, U47.9 (Q), U49.1 (OE)
unnamed: U44.3, U44.4, U50.19 (CE)
